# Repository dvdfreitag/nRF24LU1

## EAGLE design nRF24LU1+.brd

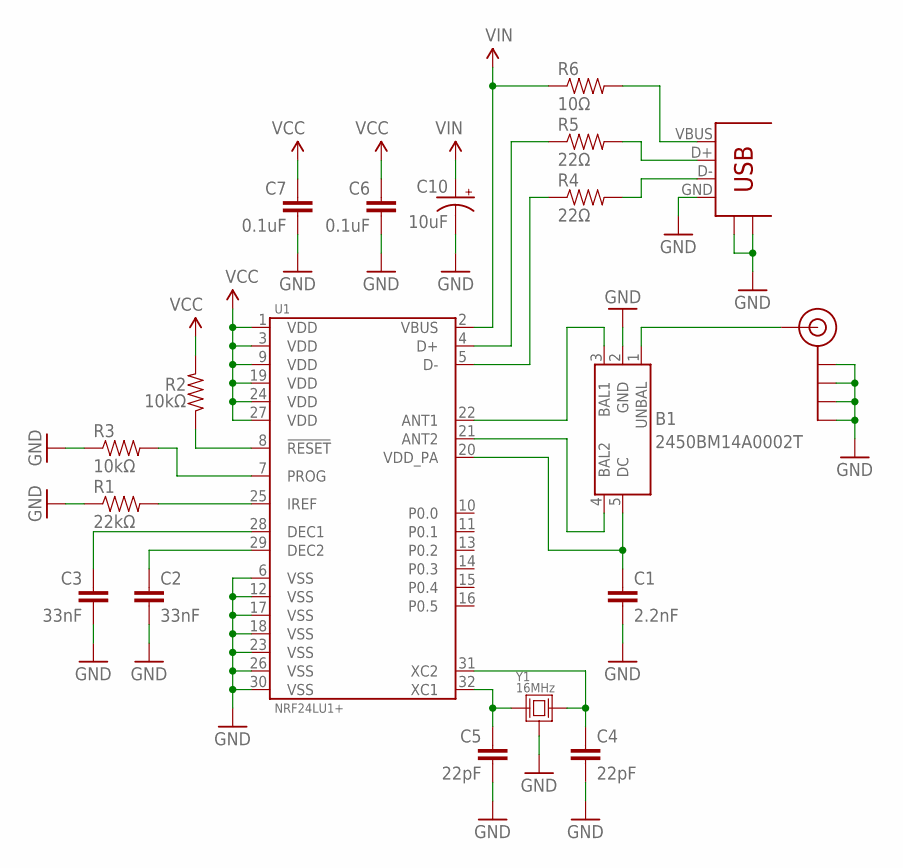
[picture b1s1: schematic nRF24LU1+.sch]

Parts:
B1: 2450BM14A0002T; BALUN-0603
C1: 2.2nF; 0402-CAP
C2, C3: 33nF; 0402-CAP
C4, C5: 22pF; 0402-CAP
C6, C7: 0.1uF; 0402-CAP
C10: 10uF; 0805-CAP_POL
J1: USB+SHIELD-A-H; USB-A-H
J$1: SMA_EDGE; SMA-EDGE
R1: 22kΩ; 0402-RES
R2, R3: 10kΩ; 0402-RES
R4, R5: 22Ω; 0402-RES
R6: 10Ω; 0402-RES
U1: NRF24LU1+; QFN-32
Y1: 16MHz; FA-238

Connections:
GND: B1.2 (GND), C1.2, C2.2, C3.2, C4.2, C5.2, C6.2, C7.2, C10.C (-), J1.GND, J1.GND2 (S1), J1.GND3 (S2), J$1.GND@0 (GND), J$1.GND@1 (GND), J$1.GND@2 (GND), J$1.GND@3 (GND), R1.1, R3.1, U1.6 (VSS), U1.12 (VSS), U1.17 (VSS), U1.18 (VSS), U1.23 (VSS), U1.26 (VSS), U1.30 (VSS), Y1.2 (GND), Y1.4 (GND)
unnamed: R2.1, U1.8 (!RESET)
unnamed: C2.1, U1.29 (DEC2)
unnamed: C3.1, U1.28 (DEC1)
unnamed: R1.2, U1.25 (IREF)
unnamed: R3.2, U1.7 (PROG)
unnamed: C5.1, U1.32 (XC1), Y1.1
unnamed: C4.1, U1.31 (XC2), Y1.3 (2)
unnamed: B1.4 (BAL2), U1.21 (ANT2)
unnamed: B1.3 (BAL1), U1.22 (ANT1)
unnamed: B1.5 (DC), C1.1, U1.20 (VDD_PA)
unnamed: B1.1 (UNBAL), J$1.SIG (SIGNAL)
unnamed: J1.D+, R5.2
unnamed: J1.D-, R4.2
unnamed: J1.VBUS, R6.2
unnamed: R5.1, U1.4 (D+)
unnamed: R4.1, U1.5 (D-)
VCC: C6.1, C7.1, R2.2, U1.1 (VDD), U1.3 (VDD), U1.9 (VDD), U1.19 (VDD), U1.24 (VDD), U1.27 (VDD)
VIN: C10.A (+), R6.1, U1.2 (VBUS)

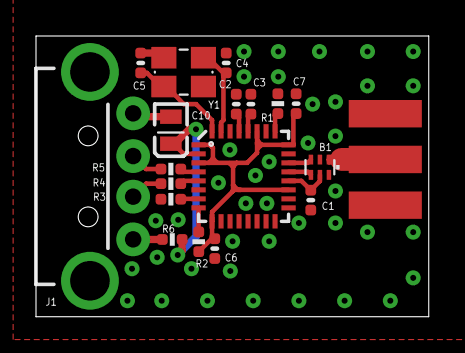
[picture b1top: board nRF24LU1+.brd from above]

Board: 2 copper layers, 21.8 x 15.6 mm, 19 parts (0 on the bottom side), 19 nets.

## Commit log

2016-08-12 Added documents
2016-08-12 Create LICENSE

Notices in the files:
parts and their libraries:
SparkFun-RF: Licensing: Creative Commons ShareAlike 4.0 International - https://creativecommons.org/licenses/by-sa/4.0
